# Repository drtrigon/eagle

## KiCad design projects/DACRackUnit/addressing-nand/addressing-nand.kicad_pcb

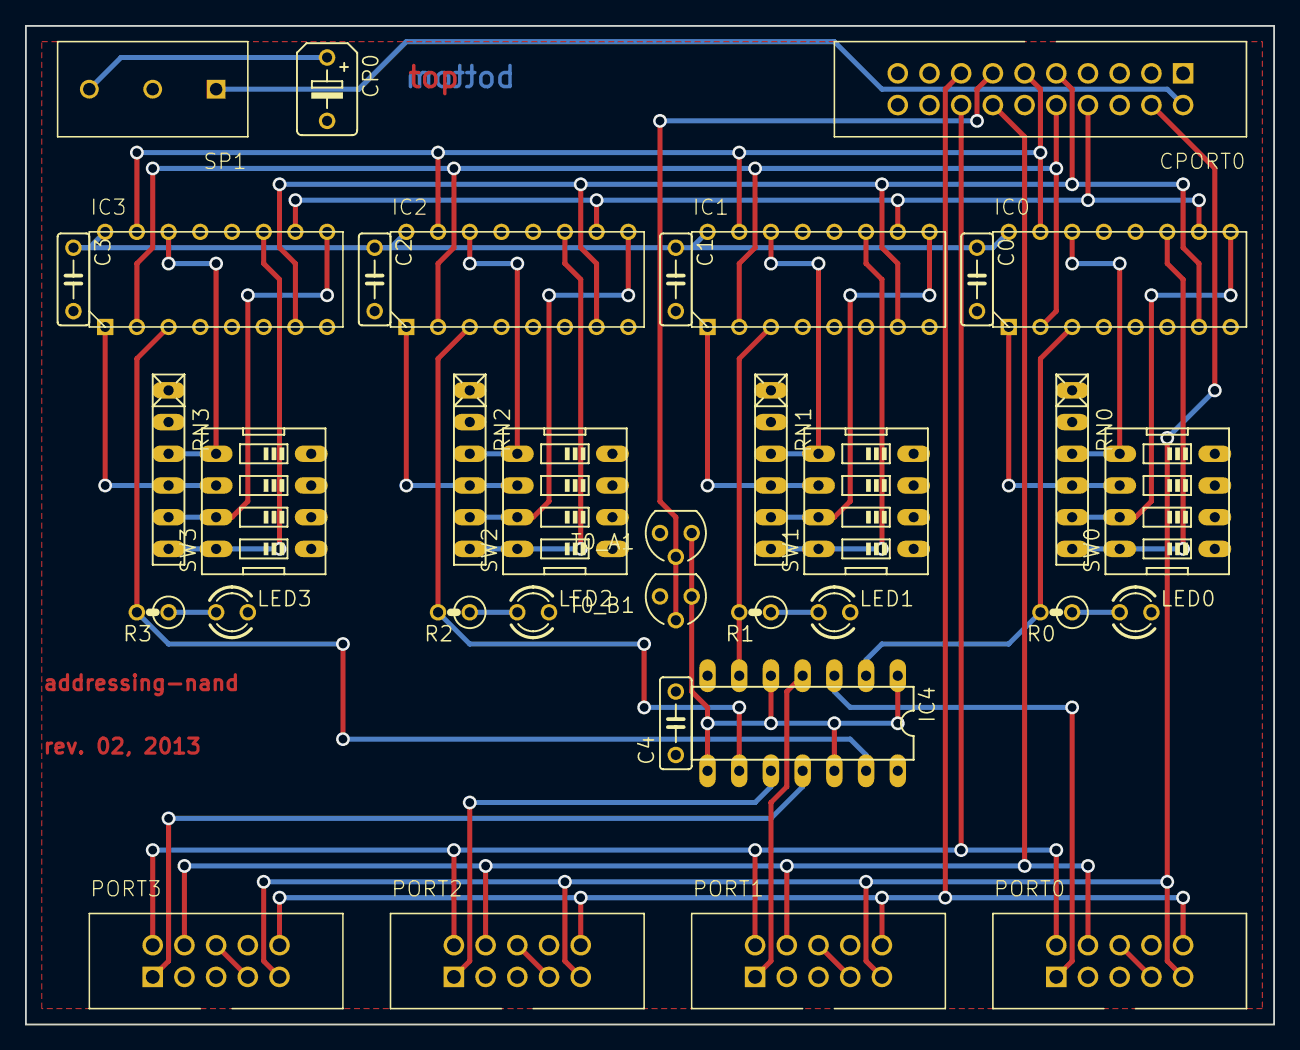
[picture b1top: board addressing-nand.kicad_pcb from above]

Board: 2 copper layers, 100.0 x 80.0 mm, 35 parts (0 on the bottom side), 41 nets.

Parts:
C0, C1, C2, C3, C4: 100nF; C050-025X075
CP0: 10uF; B45181B
CPORT0: DIN-41651-20P
IC0, IC1, IC2, IC3: MC14585; PDIP-16
IC4: 4011N; DIL14
LED0, LED1, LED2, LED3: 2mA (max); LED3MM
PORT0, PORT1, PORT2, PORT3: DIN-41651-10P
R0, R1, R2, R3: 1k-2k; 0207_2V
RN0, RN1, RN2, RN3: 9k9; RN-6
SP1: WAGO-3
SW0, SW1, SW2, SW3: 4pins; EDG-04
T0_A1: BS250; SOT54E
T0_B1: BS170; SOT54E

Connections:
+3V3: C0.1, C1.1, C2.1, C3.1, C4.1, CP0.+, IC0.(A=B)_IN$6, IC0.VDD$16, IC1.(A=B)_IN$6, IC1.VDD$16, IC2.(A=B)_IN$6, IC2.VDD$16, IC3.(A=B)_IN$6, IC3.VDD$16, IC4.14, PORT0.P$6, PORT0.P$7, PORT1.P$6, PORT1.P$7, PORT2.P$6, PORT2.P$7, PORT3.P$6, PORT3.P$7, SP1.P$3, SW0.1, SW0.2, SW0.3, SW0.4, SW1.1, SW1.2, SW1.3, SW1.4, SW2.1, SW2.2, SW2.3, SW2.4, SW3.1, SW3.2, SW3.3, SW3.4, T0_A1.S
+5V: CPORT0.P$2, SP1.P$1
/B0.0: IC0.B0$11, RN0.6, SW0.8
/B0.1: IC0.B1$9, RN0.5, SW0.7
/B0.2: IC0.B2$1, RN0.4, SW0.6
/B0.3: IC0.B3$14, RN0.3, SW0.5
/B1.0: IC1.B0$11, RN1.6, SW1.8
/B1.1: IC1.B1$9, RN1.5, SW1.7
/B1.2: IC1.B2$1, RN1.4, SW1.6
/B1.3: IC1.B3$14, RN1.3, SW1.5
/B2.0: IC2.B0$11, RN2.6, SW2.8
/B2.1: IC2.B1$9, RN2.5, SW2.7
/B2.2: IC2.B2$1, RN2.4, SW2.6
/B2.3: IC2.B3$14, RN2.3, SW2.5
/B3.0: IC3.B0$11, RN3.6, SW3.8
/B3.1: IC3.B1$9, RN3.5, SW3.7
/B3.2: IC3.B2$1, RN3.4, SW3.6
/B3.3: IC3.B3$14, RN3.3, SW3.5
/CS: IC4.1, IC4.5, IC4.8, IC4.12, T0_A1.D, T0_B1.D
/CS0: IC0.(A=B)_OUT$3, IC4.2, R0.2
/CS0_INV: IC4.3, PORT0.P$1
/CS1: IC1.(A=B)_OUT$3, IC4.6, R1.2
/CS1_INV: IC4.4, PORT1.P$1
/CS2: IC2.(A=B)_OUT$3, IC4.9, R2.2
/CS2_INV: IC4.10, PORT2.P$1
/CS3: IC3.(A=B)_OUT$3, IC4.13, R3.2
/CS3_INV: IC4.11, PORT3.P$1
/CS_INV: CPORT0.P$13, T0_A1.G, T0_B1.G
/P4: CPORT0.P$8, IC0.A0$10, IC1.A0$10, IC2.A0$10, IC3.A0$10
/P5: CPORT0.P$9, IC0.A1$7, IC1.A1$7, IC2.A1$7, IC3.A1$7
/P6: CPORT0.P$10, IC0.A2$2, IC1.A2$2, IC2.A2$2, IC3.A2$2
/P7: CPORT0.P$11, IC0.A3$15, IC1.A3$15, IC2.A3$15, IC3.A3$15
/RESET_INV: CPORT0.P$4, PORT0.P$9, PORT1.P$9, PORT2.P$9, PORT3.P$9
/SCLK: CPORT0.P$16, PORT0.P$2, PORT1.P$2, PORT2.P$2, PORT3.P$2
/SDIN: CPORT0.P$14, PORT0.P$4, PORT1.P$4, PORT2.P$4, PORT3.P$4
/SDO: CPORT0.P$15, PORT0.P$10, PORT1.P$10, PORT2.P$10, PORT3.P$10
GND: C0.2, C1.2, C2.2, C3.2, C4.2, CP0.-, CPORT0.P$1, IC0.(A<B)_IN$5, IC0.(A>B)_IN$4, IC0.VSS$8, IC1.(A<B)_IN$5, IC1.(A>B)_IN$4, IC1.VSS$8, IC2.(A<B)_IN$5, IC2.(A>B)_IN$4, IC2.VSS$8, IC3.(A<B)_IN$5, IC3.(A>B)_IN$4, IC3.VSS$8, IC4.7, LED0.K, LED1.K, LED2.K, LED3.K, PORT0.P$5, PORT1.P$5, PORT2.P$5, PORT3.P$5, RN0.1, RN0.2, RN1.1, RN1.2, RN2.1, RN2.2, RN3.1, RN3.2, SP1.P$2, T0_B1.S
unnamed: LED0.A, R0.1
unnamed: LED1.A, R1.1
unnamed: LED2.A, R2.1
unnamed: LED3.A, R3.1

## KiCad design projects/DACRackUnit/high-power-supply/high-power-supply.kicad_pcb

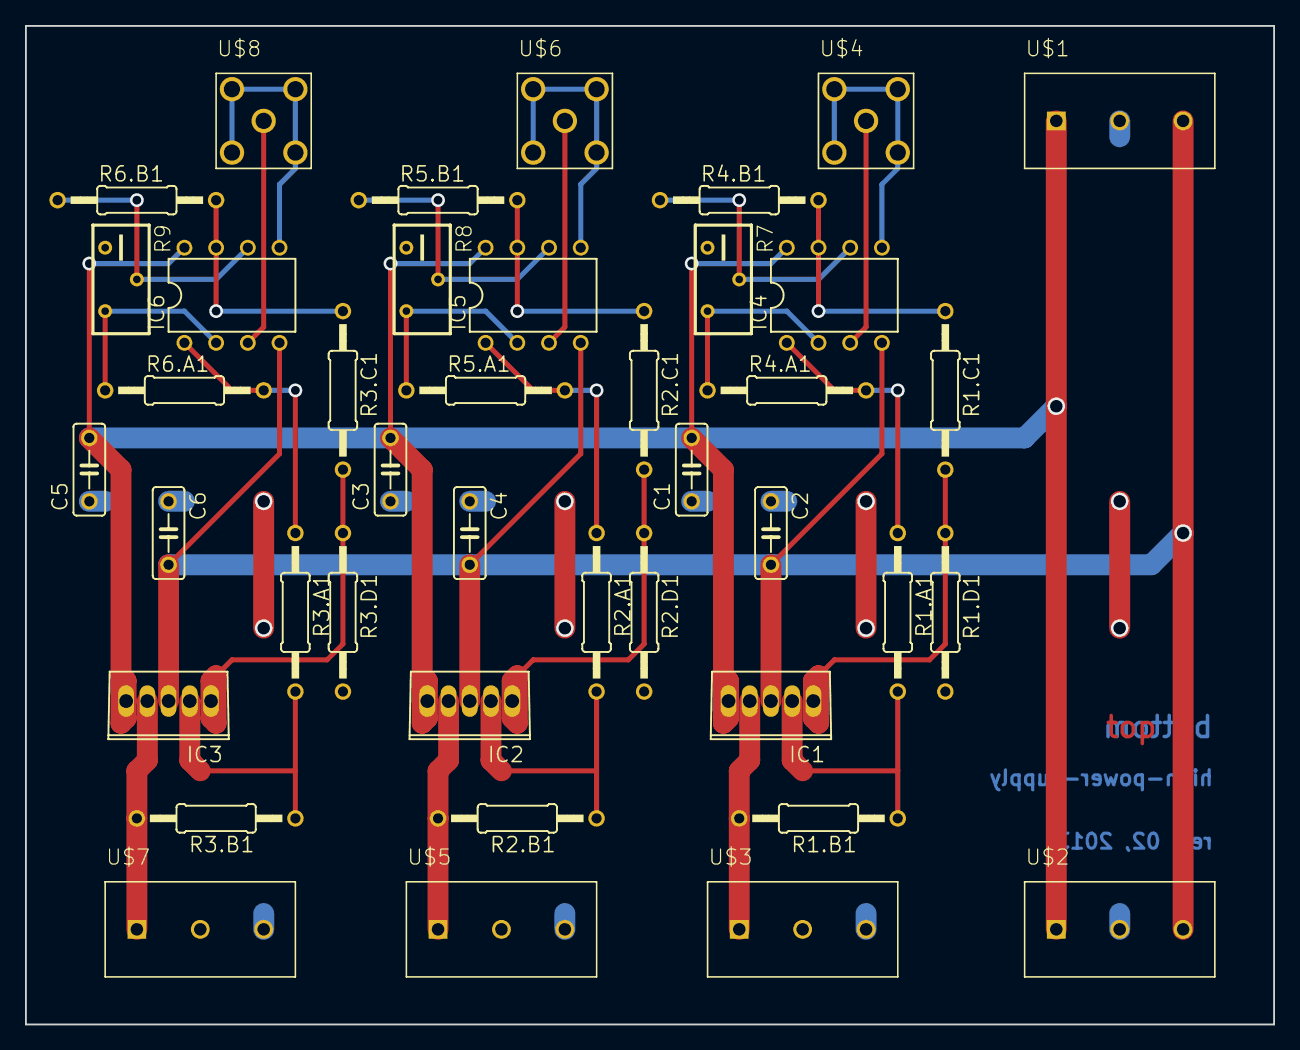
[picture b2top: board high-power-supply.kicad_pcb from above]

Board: 2 copper layers, 100.0 x 80.0 mm, 41 parts (0 on the bottom side), 30 nets.

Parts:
C1, C2, C3, C4, C5, C6: 10muF; C050-025X075
IC1, IC2, IC3: OPA544T; TO220-G5
IC4, IC5, IC6: LM358N; DIL08
R1.A1, R1.B1, R1.C1, R1.D1, R2.A1, R2.B1, R2.C1, R2.D1, R3.A1, R3.B1, R3.C1, R3.D1: 25k ?; 0207_12
R4.A1, R4.B1, R5.A1, R5.B1, R6.A1, R6.B1: 10k ?; 0207_12
R7, R8, R9: 1M ?; RTRIM3296Y
U$1, U$2, U$3, U$5, U$7: WAGO-3
U$4, U$6, U$8: SMB-50OHM; B-30

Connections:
+15V: C1.2, C3.2, C5.2, IC1.5, IC2.5, IC3.5, IC4.8, IC5.8, IC6.8, U$1.P$1, U$2.P$1
-15V: C2.2, C4.2, C6.2, IC1.3, IC2.3, IC3.3, IC4.4, IC5.4, IC6.4, U$1.P$3, U$2.P$3
/+V1: IC4.3, U$4.P$1
/+V2: IC5.3, U$6.P$1
/+V3: IC6.3, U$8.P$1
/-V1: IC4.5, U$4.P$2, U$4.P$3, U$4.P$4, U$4.P$5
/-V2: IC5.5, U$6.P$2, U$6.P$3, U$6.P$4, U$6.P$5
/-V3: IC6.5, U$8.P$2, U$8.P$3, U$8.P$4, U$8.P$5
/VOUT1: IC1.4, R1.B1.2, U$3.P$1
/VOUT2: IC2.4, R2.B1.2, U$5.P$1
/VOUT3: IC3.4, R3.B1.2, U$7.P$1
GND: C1.1, C2.1, C3.1, C4.1, C5.1, C6.1, R1.D1.2, R2.D1.2, R3.D1.2, U$1.P$2, U$2.P$2, U$3.P$3, U$5.P$3, U$7.P$3
unnamed: IC1.1, R1.C1.2, R1.D1.1
unnamed: IC1.2, R1.A1.2, R1.B1.1
unnamed: IC2.1, R2.C1.2, R2.D1.1
unnamed: IC2.2, R2.A1.2, R2.B1.1
unnamed: IC3.1, R3.C1.2, R3.D1.1
unnamed: IC3.2, R3.A1.2, R3.B1.1
unnamed: IC4.1, R1.A1.1, R4.A1.2
unnamed: IC4.2, R4.A1.1, R7.3
unnamed: IC4.6, R4.B1.1, R7.2
unnamed: IC4.7, R1.C1.1, R4.B1.2
unnamed: IC5.1, R2.A1.1, R5.A1.2
unnamed: IC5.2, R5.A1.1, R8.3
unnamed: IC5.6, R5.B1.1, R8.2
unnamed: IC5.7, R2.C1.1, R5.B1.2
unnamed: IC6.1, R3.A1.1, R6.A1.2
unnamed: IC6.2, R6.A1.1, R9.3
unnamed: IC6.6, R6.B1.1, R9.2
unnamed: IC6.7, R3.C1.1, R6.B1.2

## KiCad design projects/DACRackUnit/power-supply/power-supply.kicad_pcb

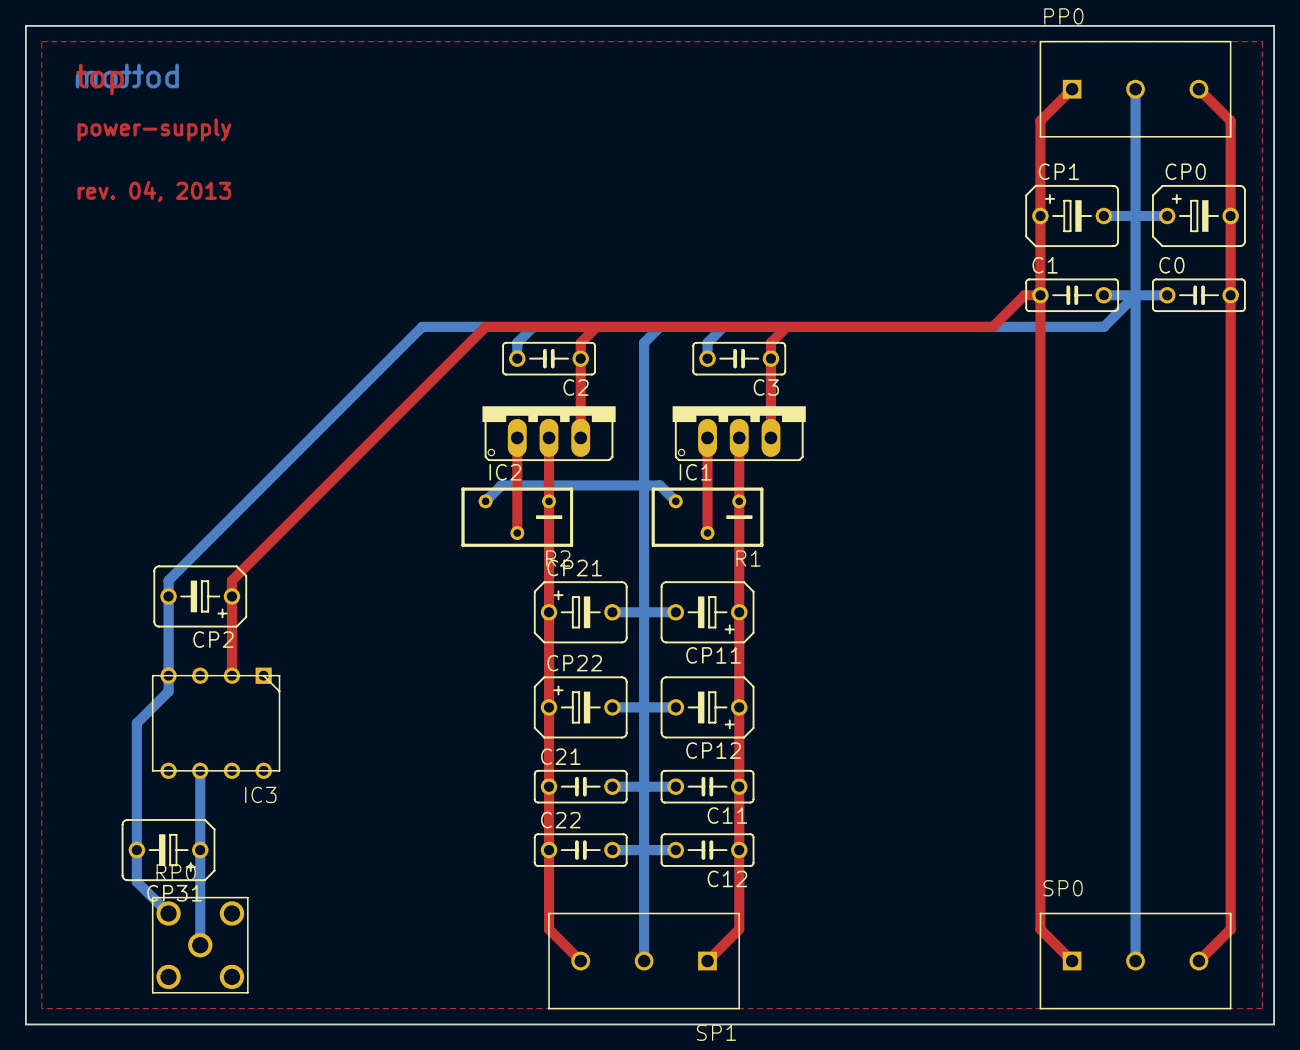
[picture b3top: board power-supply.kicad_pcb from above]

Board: 2 copper layers, 100.0 x 80.0 mm, 25 parts (0 on the bottom side), 8 nets.

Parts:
C0, C1, C2, C3, C11, C12, C21, C22: 100nF; C050-025X075
CP0, CP1, CP11, CP12, CP21, CP22: 10uF; B45181B
CP2, CP31: 2.2uF; B45181B
IC1, IC2: LM317; 317TS
IC3: VREF-REF02-MAX6350; PDIP-8
PP0: WAGO-3
R1, R2: 1k; RTRIM3296Y
RP0: SMB-50OHM; B-30
SP0, SP1: WAGO-3

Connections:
+3V3: C21.1, C22.1, CP21.+, CP22.+, IC2.2, R2.1, SP1.P$3
+5V: C11.1, C12.1, CP11.+, CP12.+, IC1.2, R1.1, SP1.P$1
+5V/1: CP31.+, IC3.V_OUT$6, RP0.P$1
+15V: C1.1, C2.1, C3.1, CP1.+, CP2.+, IC1.3, IC2.3, IC3.V_IN$2, PP0.P$1, SP0.P$1
-15V: C0.2, CP0.-, PP0.P$3, SP0.P$3
GND: C0.1, C1.2, C2.2, C3.2, C11.2, C12.2, C21.2, C22.2, CP0.+, CP1.-, CP2.-, CP11.-, CP12.-, CP21.-, CP22.-, CP31.-, IC3.GND$4, PP0.P$2, R1.3, R2.3, RP0.P$2, RP0.P$3, RP0.P$4, RP0.P$5, SP0.P$2, SP1.P$2
unnamed: IC1.1, R1.2
unnamed: IC2.1, R2.2

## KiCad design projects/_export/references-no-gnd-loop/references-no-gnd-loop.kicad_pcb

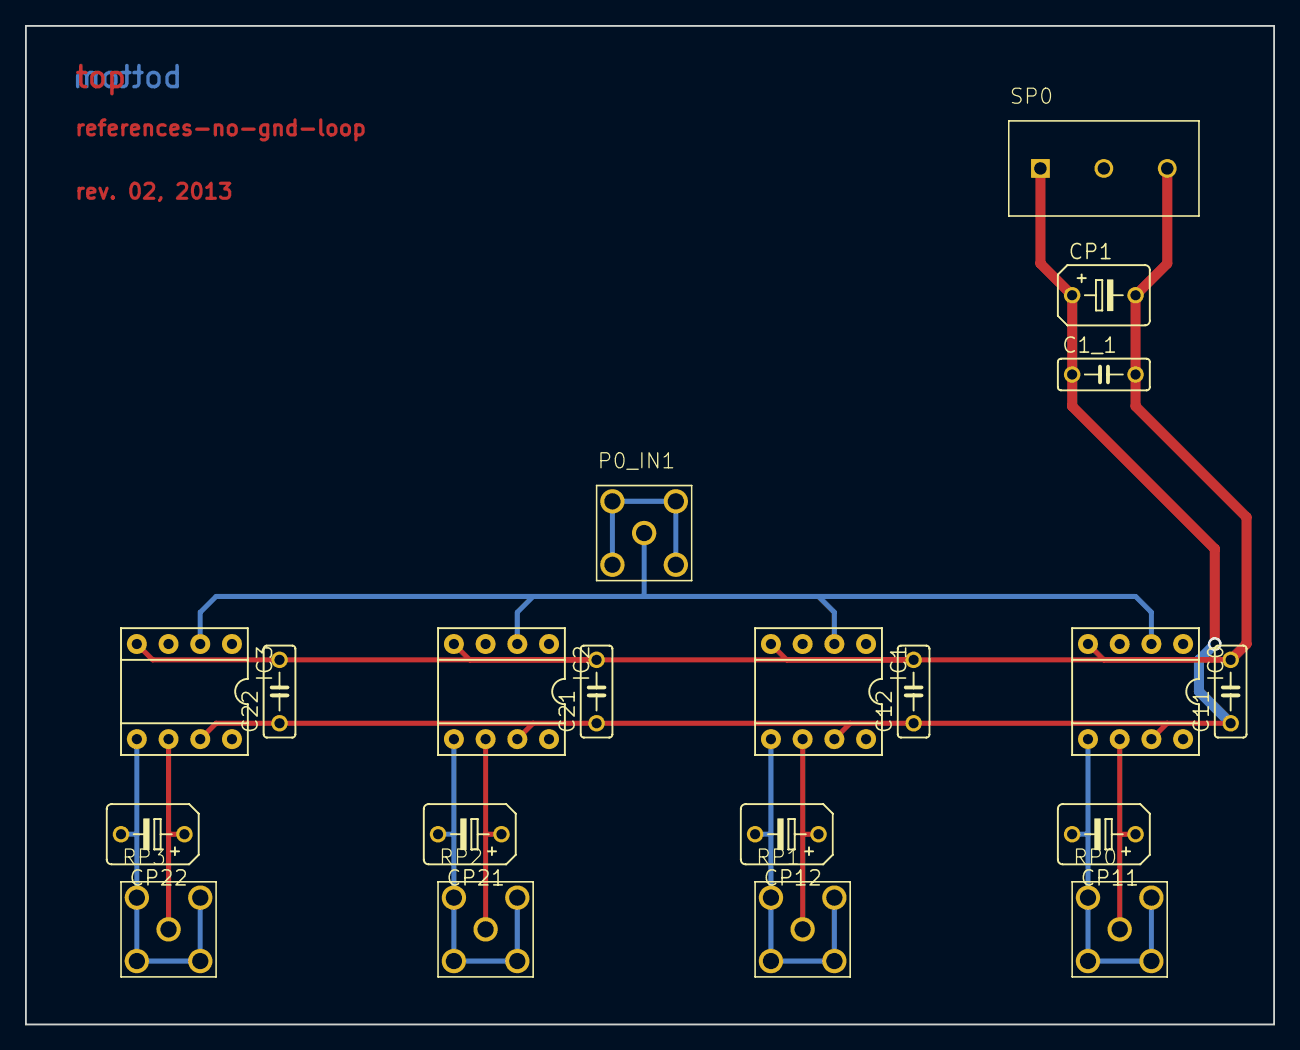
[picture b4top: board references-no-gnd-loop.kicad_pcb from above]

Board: 2 copper layers, 100.0 x 80.0 mm, 20 parts (0 on the bottom side), 12 nets.

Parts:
C1_1, C11, C12, C21, C22: 100nF; C050-025X075
CP1: 10uF; B45181B
CP11, CP12, CP21, CP22: 2.2uF; B45181B
IC0, IC1, IC2, IC3: INA118P; DIL08
P0_IN1: SMB-50OHM; B-30
RP0, RP1, RP2, RP3: SMB-50OHM; B-30
SP0: WAGO-3

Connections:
+15V: C1_1.1, C11.1, C12.1, C21.1, C22.1, CP1.+, IC0.7, IC1.7, IC2.7, IC3.7, SP0.P$1
-15V: C1_1.2, C11.2, C12.2, C21.2, C22.2, CP1.-, IC0.4, IC1.4, IC2.4, IC3.4, SP0.P$3
/RGND0: CP11.-, IC0.5, RP0.P$2, RP0.P$3, RP0.P$4, RP0.P$5
/RGND1: CP12.-, IC1.5, RP1.P$2, RP1.P$3, RP1.P$4, RP1.P$5
/RGND2: CP21.-, IC2.5, RP2.P$2, RP2.P$3, RP2.P$4, RP2.P$5
/RGND3: CP22.-, IC3.5, RP3.P$2, RP3.P$3, RP3.P$4, RP3.P$5
/VOUT0: CP11.+, IC0.6, RP0.P$1
/VOUT1: CP12.+, IC1.6, RP1.P$1
/VOUT2: CP21.+, IC2.6, RP2.P$1
/VOUT3: CP22.+, IC3.6, RP3.P$1
GND: IC0.3, IC1.3, IC2.3, IC3.3, P0_IN1.P$2, P0_IN1.P$3, P0_IN1.P$4, P0_IN1.P$5
unnamed: IC0.2, IC1.2, IC2.2, IC3.2, P0_IN1.P$1
